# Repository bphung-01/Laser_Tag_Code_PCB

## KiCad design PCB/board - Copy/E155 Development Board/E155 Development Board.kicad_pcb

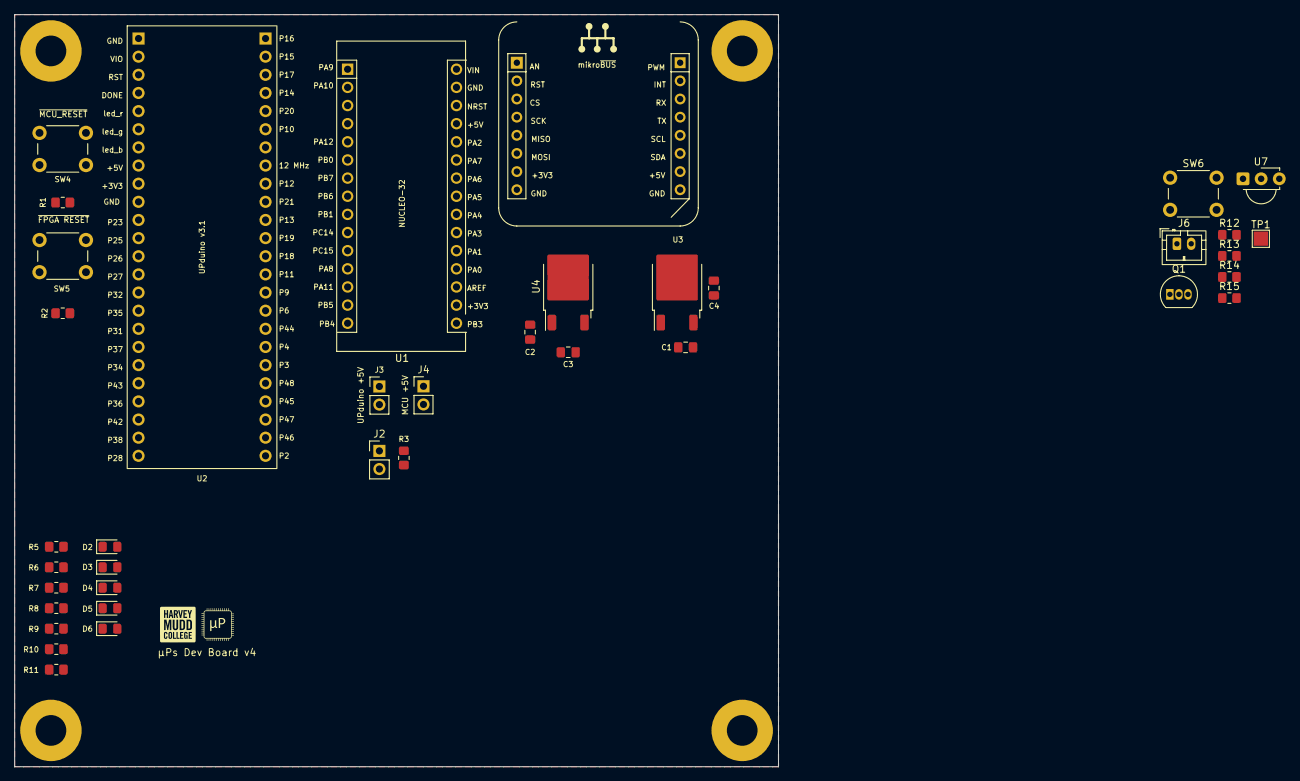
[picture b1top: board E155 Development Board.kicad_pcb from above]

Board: 2 copper layers, 106.9 x 105.3 mm, 42 parts (0 on the bottom side), 36 nets, no tracks yet.

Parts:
C1, C2, C3, C4: 10µ; C_0805_2012Metric_Pad1.18x1.45mm_HandSolder
D2: LED (G); LED_0805_2012Metric_Pad1.15x1.40mm_HandSolder
D3: LED (B); LED_0805_2012Metric_Pad1.15x1.40mm_HandSolder
D4: IR LED; LED_0805_2012Metric_Pad1.15x1.40mm_HandSolder
D5: R(or B) LED; LED_0805_2012Metric_Pad1.15x1.40mm_HandSolder
D6: LED; LED_0805_2012Metric_Pad1.15x1.40mm_HandSolder
H1, H2, H3, H4: MountingHole; MountingHole_4.3mm_M4_Pad
J2: ESP RST Jumper; PinHeader_1x02_P2.54mm_Vertical
J3: FPGA Jumper; PinHeader_1x02_P2.54mm_Vertical
J4: MCU Jumper; PinHeader_1x02_P2.54mm_Vertical
J6: 2S Lipo; JST_PH_B2B-PH-K_1x02_P2.00mm_Vertical
Q1: 2N3906; TO-92_Inline
R1, R5, R6: 1k; R_0805_2012Metric_Pad1.20x1.40mm_HandSolder
R2, R3, R8, R9, R11: 10k; R_0805_2012Metric_Pad1.20x1.40mm_HandSolder
R7: 10; R_0805_2012Metric_Pad1.20x1.40mm_HandSolder
R10: 100; R_0805_2012Metric_Pad1.20x1.40mm_HandSolder
R12, R13, R15: 330; R_0805_2012Metric_Pad1.20x1.40mm_HandSolder
R14: 1.2k; R_0805_2012Metric_Pad1.20x1.40mm_HandSolder
SW4, SW5: SW_Push; SW_PUSH_6mm_H4.3mm
SW6: Trigger; SW_PUSH_6mm_H4.3mm
TP1: BATT_RAW; TestPoint_Pad_2.0x2.0mm
U1: NUCLEO-LxxxKx; NUCLEO-32
U2: UPduino_v3.1
U3: LD1117DT50TR; TO-252-2
U4: LD1117DT33CTR; TO-252-2
U5: mikroBUS_SOCKET; MIKROBUS_HOST_CONN
U7: TSOP38238; Vishay_MINICAST-3Pin

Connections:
+3V3: C2.1, D3.2 (A), Q1.1 (E), R1.1, R2.1, R3.1, R11.1, U4.2 (VO), U5.7 (+3.3V), U7.3 (Vs)
+5V: C4.1, D2.2 (A), J3.1, J4.1, U3.2 (VO), U5.10 (+5V)
/BATT: C1.1, C3.1, U3.3 (VI), U4.3 (VI)
/BATT_RAW: J6.1, TP1.1 (1_1)
/FPGA_+5V: J3.2, U2.8 (+5V)
/MCU_+5V: J4.2, U1.27 (+5V)
/MIKROBUS_RST: J2.2, U5.2 (RST)
/P10: U1.14 (D11/PB5/MOSI), U2.43 (GPIO_10), U5.6 (MOSI)
/P12: U1.15 (D12/PB4/MISO), U2.40 (GPIO_12), U5.5 (MISO)
/P13: D6.2 (A), U2.38 (GPIO_13)
/P20: U1.13 (D10/PA11/CS), U2.44 (GPIO_20), U5.3 (CS)
/P21: U1.16 (D13/PB3/SCK), U2.39 (GPIO_21), U5.4 (SCK)
/P32: U2.15 (GPIO_32), U7.1 (OUT)
/P34: R13.2, U2.19 (GPIO_34)
/P37: R11.2, SW6.2, U2.18 (GPIO_37)
/P43: D5.2 (A), U2.20 (GPIO_43)
/PA0: U1.19 (A0/PA0), U5.1 (AN)
/PA1: U1.20 (A1/PA1), U5.16 (PWM)
/PA3: U1.21 (A2/PA3), U5.15 (INT)
/PA4: R9.1, U1.22 (A3/PA4)
/PA5: U1.23 (A4/PA5/SDA), U5.11 (SDA)
/PA6: U1.24 (A5/PA6/SCL), U5.12 (SCL)
/PA9: U1.1 (D1/PA9/TX1), U5.13 (TX)
/PA10: U1.2 (D0/PA10/RX1), U5.14 (RX)
/~FPGA_RESET: R2.2, SW5.2, U2.3 (~RST)
/~MCU_RESET: R1.2, SW4.2, U1.3 (~RESET), U1.28 (~RESET)
GND: C1.2, C2.2, C3.2, C4.2, H1.1 (1_1), H2.1 (1_1), H3.1 (1_1), H4.1 (1_1), J6.2, R5.2, R6.2, R8.2, R10.2, R12.2, R15.2, SW4.1, SW5.1, SW6.1, U1.4 (GND), U1.29 (GND), U2.1 (GND), U2.10 (GND), U2.42 (GND), U3.1 (GND), U4.1 (GND), U5.8 (GND), U5.9 (GND), U7.2 (GND)
unnamed: D2.1 (K), R5.1
unnamed: D3.1 (K), R6.1
unnamed: D4.2 (A), Q1.3 (C)
unnamed: D4.1 (K), R10.1
unnamed: D5.1 (K), R12.1
unnamed: D6.1 (K), R15.1
unnamed: J2.1, R3.2
unnamed: Q1.2 (B), R13.1
unnamed: R8.1, R9.2
